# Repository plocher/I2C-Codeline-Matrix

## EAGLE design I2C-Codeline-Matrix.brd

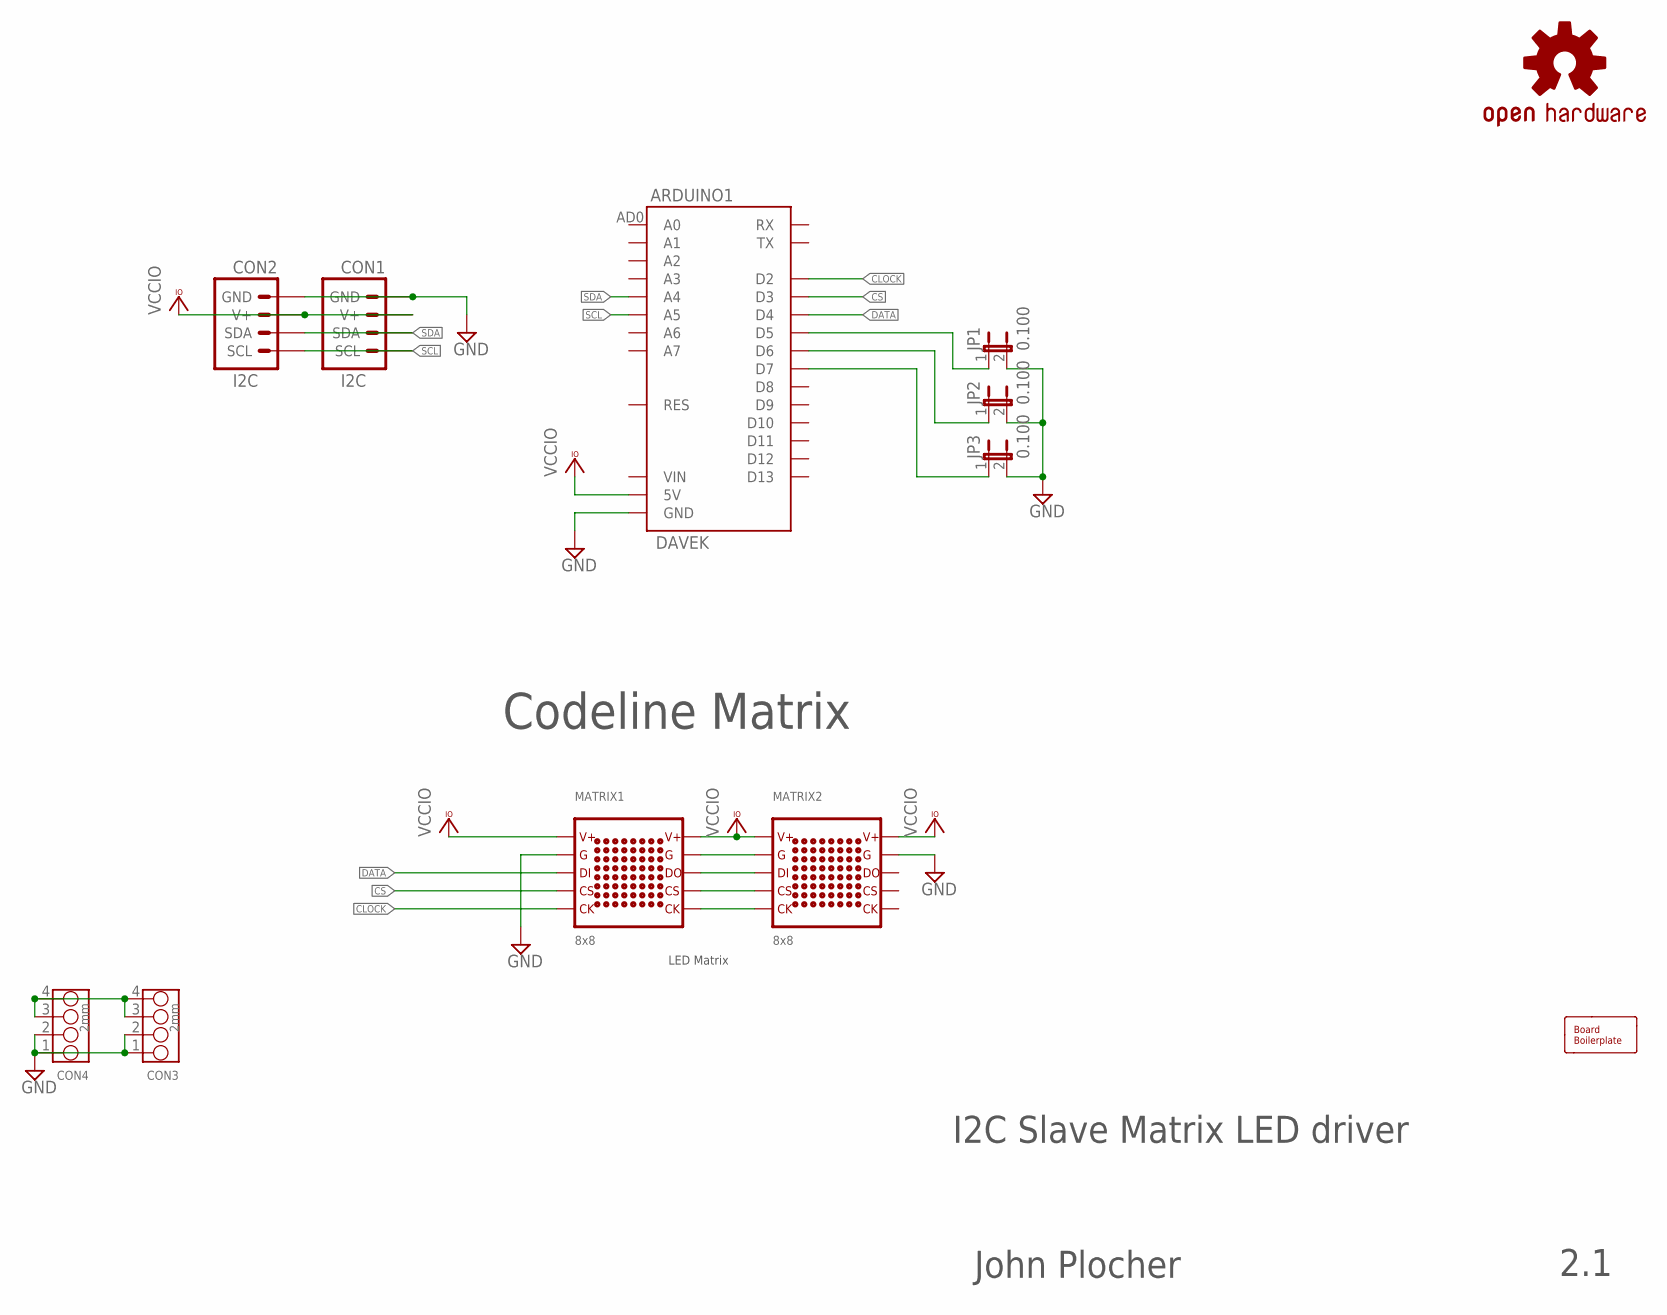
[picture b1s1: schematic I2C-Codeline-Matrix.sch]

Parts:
ARDUINO1: DAVEK; ARDUINO_PRO_MINI_DAVEK
BOARD: BOARD; BOARD-DINRAIL-3.17INX8CM-NOHOLES
CON1, CON2: I2C; I2C-L
CON3, CON4: 2mm; 4P-2.0
JP1, JP2, JP3: 0.100; 1X02_LOCK
MATRIX1, MATRIX2: 8x8; LEDMATRIX
OSHW1: OSHW; OSHW-LOGO-L

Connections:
CLOCK: ARDUINO1.D2, MATRIX1.CLK@1 (CLK)
CS: ARDUINO1.D3, MATRIX1.CS@1 (CS)
DATA: ARDUINO1.D4, MATRIX1.DI (DIN)
GND: ARDUINO1.GND@1 (GND), ARDUINO1.GND@2 (GND), ARDUINO1.GND@4 (GND), CON1.GND, CON1.GND@1 (GND), CON2.GND, CON2.GND@1 (GND), CON3.1, CON3.2, CON4.1, CON4.2, JP1.2, JP2.2, JP3.2, MATRIX1.G@1 (G), MATRIX1.G@2 (G), MATRIX2.G@1 (G), MATRIX2.G@2 (G)
unnamed: CON3.3, CON3.4, CON4.3, CON4.4
unnamed: MATRIX1.DO (DOUT), MATRIX2.DI (DIN)
unnamed: ARDUINO1.D5, JP1.1
unnamed: ARDUINO1.D6, JP2.1
unnamed: ARDUINO1.D7, JP3.1
unnamed: MATRIX1.CS@2 (CS), MATRIX2.CS@1 (CS)
unnamed: MATRIX1.CLK@2 (CLK), MATRIX2.CLK@1 (CLK)
SCL: ARDUINO1.AD5 (A5), CON1.SCL, CON1.SCL@1 (SCL), CON2.SCL, CON2.SCL@1 (SCL)
SDA: ARDUINO1.AD4 (A4), CON1.SDA, CON1.SDA@1 (SDA), CON2.SDA, CON2.SDA@1 (SDA)
VCCIO: ARDUINO1.5V, CON1.V+, CON1.V+@1 (V+), CON2.V+, CON2.V+@1 (V+), MATRIX1.V+@1 (V+), MATRIX1.V+@2 (V+), MATRIX2.V+@1 (V+), MATRIX2.V+@2 (V+)

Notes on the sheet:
I2C Slave Matrix LED driver
John Plocher
2.1
Codeline Matrix
LED Matrix

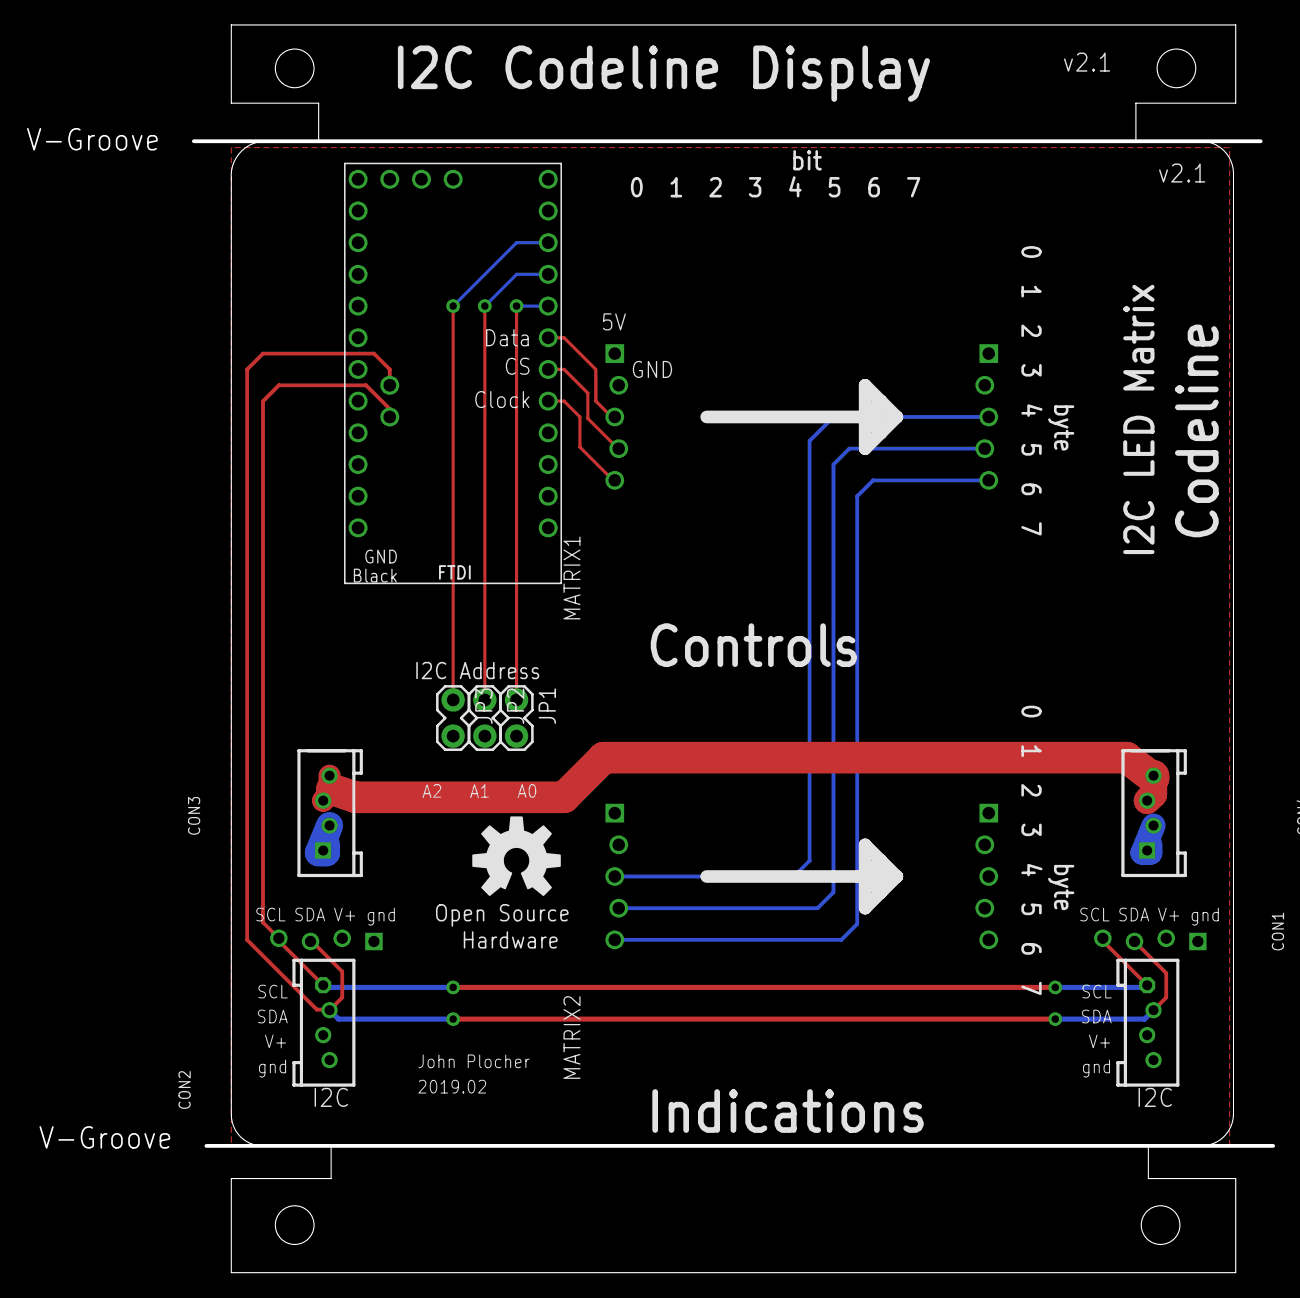
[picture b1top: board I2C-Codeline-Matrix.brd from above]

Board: 2 copper layers, 86.5 x 100.0 mm, 12 parts (0 on the bottom side), 14 nets.

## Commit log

2019-12-07 Added graphic image
2019-12-07 Added graphic
2020-05-04 updated tags
2020-10-05 added values for connectors
2020-10-06 normalized values
